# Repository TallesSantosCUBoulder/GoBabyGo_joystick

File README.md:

# GoBabyGo Joystick-Controlled Car
**ENGR140: First Year Engineering Projects - Colorado Mesa University**  
**Sponsor:** Talles Santos  
**Project Team:** Team Snow Munchers  
**Team Members:** Michael Riley (Civil Engineering)  
&emsp;&emsp;&emsp;&emsp;&emsp;&emsp;&emsp;&emsp; Francisco Cuen (Mechanical Engineering)  
&emsp;&emsp;&emsp;&emsp;&emsp;&emsp;&emsp;&emsp; Jaclyn Pellegrini (Mechanical Engineering)  
&emsp;&emsp;&emsp;&emsp;&emsp;&emsp;&emsp;&emsp;Caleb Kasayka (Mechanical Engineering)  
&emsp;  
&emsp;
&emsp;  
**Note: A large part of this README file references the [User Manual](/Reports/Users%20manual.pdf) and [Final Report](/Reports/Final%20Report%20First%20Draft%20-%20Snow%20Munchers.pdf) written by the members of the Snow Munchers Team. The printed circuit board (PCB) was designed, and the README was written and compiled, by Electrical and Computer Engineering Senior [Alyssa Jackson](https://github.com/aJax-EXE).**

## Introduction
“GoBabyGo” is a non-profit organization dedicated to providing children with limited mobility the opportunity to play independently by adapting motorized toy cars. Many children with mobility challenges struggle to press the pedal and steer simultaneously, making it difficult to operate the vehicle without constant assistance. Typical “GoBabyGo” modifications reroute the pedal wiring to a button mounted on the steering wheel, simplifying acceleration and improving usability.  

After multiple iterations, the final design operated successfully and remained within budget. It reliably controlled forward/backward motion and steering, and testing showed consistent performance with minimal drift. The system was safe, intuitive, and easy for children to use. Future work should focus on simplifying the steering circuit and adapting the design for broader use across different ride‑on car models to benefit more children.  

*A standin image of the completed modified car*  

## Project Overview
While the standard modifications help many children, some still find it difficult to press a button and steer at the same time. This project aims to create a more intuitive control system by replacing both the pedal and steering wheel with a single joystick. The joystick must control forward and backward motion as well as left and right steering, operate safely under 12 V and 3 A, and be implemented for under $200.  

### Design Requirements
Along with the functions that the car needs to reach from the the project overview, the following and specific requirements were needed:  
* Directional Control
    * Provide forward, reverse, left, and right motion; each direction successfully actuates correct motor behavior 10/10 trials with a response rate of .5 seconds. 
* Consistent Steering & Speed Response
    * Vehicle follows the same path in 5 repeated trials within acceptable tolerance (e.g., ±6 inches lateral drift over 10-15ft).
* 12V Maximum Power
    * Must not exceed 12V thought out the electrical system.
* Dashboard Fit
    * Total joystick assembly dimensions must not exceed 2.75 in (height) × 3.125 in (width). Zero interference points and no natural obstructions.
* Heat Limit
    * Must not exceed 113° over 15 minute time intervals.

###  Electrical Solutions
For this car, a modification was made for the movement. Using a joystick instead of a steering wheel and foot-powered pedals, the car can move forwards and backwards without restrictions, but turning left and right is altered. Instead of turning left and right without restriction, moving or holding the joystick in either direction causes the car to turn for only a set amount of time before stopping and waiting for another input. __This is to help keep the motors from stalling as ... ? (Include a video/gif of the car moving in all four directions with the joystick)__  

*The Full Circuit Diagram of the car*  
&emsp;  

The full construction of the circuit requires the following components:
* [3 IBT-2 BTS7960 High Current H-Bridge Motor Drivers](/Datasheets/BTS7960%20Motor%20Driver.pdf)  
&emsp;  
      
    *The Function diagram of an H-Bridge Controller*  
    &emsp;  

    * Full representation of the function of an H-Bridge Controller can be found in the above image. When an input is received, it sends a signal to the H-bridge motor controller which recognizes the voltage as a directional input and then outputs that signal into the motor itself. This allows for safe, effective, bi-directional movement. The H-bridge has a total of 12 attachment points. two for power in, two for power to motor, two for input detection (seen as “IN”), two for inhibiting direction (“INH”, two for ISs), a ground for the logic board (GND), and a 5.5V input for the logic board (“VCC”). This design will take advantage of all the inputs / outputs except for the SIs.
* [2 LM555 Timer Chips](/Datasheets/lm555.pdf)  
&emsp;  
      
    *Diagram of a 555 timer and the respective pins*  
    &emsp;  

    * A 555 timer is an integrated circuit that takes an electrical input and outputs a pulse over a certain interval of time. This component is needed to turn the front steering motor to a certain point so that the motor doesn’t overturn the mechanical component, breaking the car, and burning out the motor. Power is inputted through the VCC pin which powers the circuit (as seen in the above image). When a signal comes through the Trigger pin, it goes through the circuit within the 555 and then a capacitor and resistor attached to the discharge and threshold pins which controls how long a pulse is sent out of the output pin. For this project, the 555 is operated in monostable mode, meaning it sends out a singular pulse and then returns to its original state. To get the pulse to last for a certain time, the equation T=1.1RC where T is time, R is the strength of the resistor, and C is the value of the capacitor. For the motor a 1 second pulse is needed so values of a100kΩ resistor and a 10µF capacitor are needed.
* [A Joystick](/Datasheets/SANWA%20JLF-TP-8YT%20Joystick%20Instruction%20Manual.pdf)  
&emsp;  
      
    *Internal switching logic of the arcade joystick*  
    &emsp;  

    * The above image illustrates the internal switching logic of the joystick. The joystick has five wires with a gauge of 23 AWG (American Wire Gauge). These wires are connected to a circuit board via a connector. This system consists of four signal wires, each for a different switch that is also connected to the circuit board. The last wire serves as a 5V-12V source wire; the input (5V-12V) will flow through this wire and in return, will output through one of the four switches (possibly two) depending on which switch is compressed or activated. 
* [An RC Car](/Datasheets/BCP%20Sky908%20User%20Manual.pdf)
    * For this project an existing car was bought and provided to the group, but the car model used costs around $250 USD.

* [2 NPN Bipolar Junction Transistors](/Datasheets/2n2222a.pdf)  
&emsp;  
      
    *The circuit diagram of the pulse shaping module used in the car*  
&emsp;  
      
    *The 3D Model that represents what the working model looks like*  
&emsp;  

    * The transistors are the necessary part of the timing circuit. For the 555 to properly work, it needs sharp, high input. This is not as simple as it would seem because our joystick is mainly used in a “toggle” sense, where the driver will hold it left to turn left. After some testing, we realized that this toggled system would lead to the output of the 555 system always being held high. To fix this, we implemented what is called a pulse shaping module. This consists mainly of a capacitor momentarily allowing a transistor to drain a power source to ground, creating a quick pulse of electricity that the 555 timers can properly understand. The above images shows the pulse shaping module implemented into the design of the circuit and the 3D model of the completed PCB with all of its components.  
* [Joystick Mount](/3dModels/Joystick%20Mount%203.STL)
&emsp;  
      
    *The SolidWorks drawing of the joystick mount*  
    &emsp;  

    * The joystick already has two existing mounting holes, 0.278 inches in diameter, implemented into the factory design. With this, a CAD drawing was produced and integrated with these existing holes (see Appendix E). The design functions similar to a washer where it will mount on the original steering wheel location. Two bolts will run through the top (the side where the joystick extrudes), and below there will be two nuts securing the simple assembly in place. The above image consists of a SolidWorks drawing of the mount.  
* A 12V to 5V Voltage Step Down
    * Must be able to handle 3A of current and 15W of power.
* 6 100k Ohm Resistors
* 4 10k Ohm Resistors
* 4 10uF Capacitors
* A 12V Battery
    * The model of car used includes a 12V 7AH battery. Most electric kid cars run on 6V, but this system is designed for 12V. To use this system with a 6V battery, a voltage step down that goes from 6V to 5V, or rather a simple voltage divider, needs to be used to run the system properly.
* 2 Rolls of 20 AWG Wire
    * One red and one black preferred.  
* Female to Female Jumper wires  

The circuit starts at the battery going into the two gearboxed motors of the car and the voltage step down. The 5V from the stepdown powers the rest of the system: all three of the motor drivers and the two 555 timer circuits. While the forward and backwards motor drivers are only activated with the direct signal from the joystick, the left and right one first goes through there respective timing circuit to give the proper timed signal.  

*The Full PCB model for the car*  
&emsp;  

The PCB holds the resistors, capacitors, and transistors that make up the timing circuit, as well as all of the connectors necessary for both powering the board, connecting the joystick to the motor drivers, and for the motor drivers themselves.

## Hardware Setup and How to Operate
For the complete instructions on how to modify the car to replicate the project, perform maintainence, and for a full list of tools needed and how to use, refer to the [User Manual](/Reports/User%20Manual%20Outline.pdf) written by the Snow Munchers.

### Recommendations for Operation
Before general use, it is recommended that:  
* The driver does not exceed 77lbs
* The car avoids liquid 
* The car is not driven in the rain	 
* The car avoids sharp drops offs like curbs

## Results
### Overview
The electric ride on car was evaluated against the specified design requirements through structed user testing and system performance checks. Each criterion, directional control, steering consistency, power limit, heat limit, and size requirement, was assessed during real world operation to ensure the design met both functional and safety expectations. Users operated the vehicle under normal conditions, allowing the team to observe control, responsiveness, and overall usability. The system was required to satisfy all evaluation criteria in order to be considered successful. Testing results showed that the ride on car met all the design requirements, demonstrating reliable performance, safe operations, and suitability for its intended use.  
&emsp;  
### CRITERIA 1 – DIRECTIONAL CONTROL
Provide forward, reverse, left, and right motion; each direction successfully actuates correct motor behavior 10/10 trials with a response rate of .5 seconds.  

* **PURPOSE OF EVALUATION**: The purpose of the directional control test is to ensure that the electric ride on car responds accurately and reliably to user inputs. Effective directional control is essential for safe operations, as it allows the user to intentionally move the vehicle forward, backward, and laterally, ensuring the car can be maneuvered smoothly during normal operation and while navigating obstacles or turns. 

* **TESTING METHODS**: The evaluation of this design criteria requires that the user manually push the joystick in each direction, forward, backward, left, and right. This was tested in two ways, a static test, elevating the car off a flat surface so that the wheels can spin freely allowing the testers to visually see the steering response. And a dynamic test, driving the car through a specially crafted course designed with turns and corners to test the steering compacity while in motion. For the setup, the car was supported above a flat surface using four wooden 2 by 4 blocks, ensuring that all the wheels were fully suspended and unrestricted in rotation. This configuration eliminated ground friction and external load effects. Allowing isolated evaluation of the motor and steering response. With the vehicle secured, the joystick was actuated individually in the forward, reverse, left, and right directions. Observations were made to confirm correct wheel rotation direction, steering actuation, and immediate system response corresponding to each input. Any unintended motion, delay, or incorrect direction would indicate a fault in the signal interpretation or motor control. For the dynamic control test the electric ride on car was operated on a flat indoor surface and driven through a predefined course designed to replicate realistic operating conditions. The course consisted of straight sections, gradual turns, and sharp corners. Requiring continuous directional input adjustments. The user controlled the vehicle solely via the joystick, executing directional changes while the car remained in motion. This test evaluated the system’s ability to interpret joystick input under load, maintain control during directional transitions, and execute smooth turning without loss of stability or responsiveness. 

* **RESULTS & DISCUSSION**: The electric ride on car demonstrated correct directional response during both static and dynamic testing. In the static response test, joystick inputs in all four directions resulted in correct wheel movement with no observed latency, incorrect rotation, or unintended behavior. During the dynamic testing, the vehicle successfully followed the predetermined course and executed directional changes while in motion. The system maintained full responsiveness and directional accuracy thought out all test runs. No failures or loss of control were observed. As a result, the directional control system achieved a 100% success rate across all tests. The results indicated that the directional control system functions as intended under both unloaded and operational conditions. The static test confirmed control signal interpretation and motor actuation, while the dynamic test verified reliable performance under load. Although quantitative data was not collected, consistent qualitative performance across multiple trials demonstrates that the system meets the directional control requirements. The ability to maintain accurate direction changes while motion indicates sufficient control logic, motor response, and system integration. Therefore, the direction control design requirement was fully satisfied.  

### CRITERIA 2 – STEERING CONSISTENCY
Vehicle follows the same path in 5 repeated trials within acceptable tolerance (e.g., ±6 inches lateral drift over 10-15ft).  

* **PURPOSE OF EVALUATION**: The purpose of the steering consistency requirement is to ensure that the vehicle responds predictably and repeatably and repeatably to identical steering inputs. Consistent steering behavior is essential for user confidence, safe operation, and accurate maneuvering. This requirement verifies that the steering system produces uniform turning behavior without variation or drift during repeated use. 

* **TESTING METHODS**: Steering consistency was assessed using a straight-line deviation test. The vehicle was commanded to drive forward with a fixed joystick input while lateral deviation from a defined centerline was measured. The test evaluates the vehicle’s ability to maintain a straight trajectory under constant input. This method demonstrates whether the steering system produces predictable and repeatable behavior, which directly impacts controllability and user confidence in the finished product. For the setup, the steering consistency test was conducted on a flat, level surface to minimize external influences. A straight reference line was established using a tape measure at a fixed distance placed longitudinally along the test path. The electric ride on was aligned so that its centerline coincided with the reference line at the starting position. The vehicle was positioned at a consistent starting distance for each trial to ensure repeatability. During testing, the car was allowed to travel forward along the reference line while lateral deviation from the centerline was visually monitored and measured relative to the ruler. All tests were performed under identical surface and environment conditions to ensure consistent results. 

* **RESULTS & DISCUSSION**: The straight-line steering consistency test produced lateral drift across multiple trials and test length ranging from approximately 10 – 15ft. measured drift values varied significantly between trials, indicating nonuniform steering behavior under constant joystick input. Server trials remained within the ±6 in acceptance tolerance, deviations were small and showed no progressive drift over the test distance. However few outliers appeared in the tests but they were ruled out for being user error and were taken note of but not deemed important to the over all trials. Within this acceptance range, deviations were small and showed no progressive drift over the test distance. The compliant data demonstrates repeatable straight line tracking performance under consistent input conditions. The in tolerance results indicate that the steering system is capable of maintaining an acceptably straight trajectory when commanded with fixed forward input. The limited magnitude of lateral deviation suggests that the mechanical steering alignment and control response are sufficient for stable, predictable operation in the finished design. These results support the conclusion that, within defined performance limits, the steering system meets the consistency requirement. Maintaining deviation with ±6 inches ensures adequate controllability and user confidence during straight line motion.  

### CRITERIA 3 – POWER LIMIT
Must not exceed 12V thought out the electrical system.  

* **PURPOSE OF EVALUATION**: The purpose of the power limit requirement is to ensure that the electric ride on car operates within safe electric and mechanical limits. Restricted power output prevents excessive speed, reduces stress on system components such as the motor, battery, and drivetrain, and minimizes potential safety risks to the user. This requirement ensures controlled performance while maintaining reliability and compliance with design constraints for the finished project. 

* **TESTING METHODS**: To test, the power limit requirement was evaluated by measuring electrical current and voltage at key point throughout the vehicles electrical system. A multimeter was used to monitor voltage and current in selected wiring segments supplying the motor and control electronics during operation. Testing verified that system voltage remained below 12 V and that operating current did not exceed the specified limit of a 3 amp under normal driving conditions. Measurements were taken while the vehicle was powered and active to ensure compliance under realistic load conditions. For the setup, power limit testing was conducted using a digital multimeter to measure voltage and current at multiple points within the vehicle’s electrical system. Measurement locations included the batter output, motor supply lines, and control circuit wiring to capture representative operating conditions. The car was powered on and operated under normal operating conditions while the multimeter probes were connected in series for current measurement and in parallel for voltage measurement. Tests were performed while the vehicle was stationary and during motion to account for load variation. All measurements were taken with the system fully assembled to reflect real operating conditions. 

* **RESULTS & DISCUSSION**: Power limit testing confirmed that the electrical system operated within the defined constraints during all the testing conditions. Measured system voltage remained below the maximum allowable limit of 12V, and operating current did not exceed 3 amps at any monitored location. All measurements points across the battery, motor supply, and control wiring remained within the specified limits under both stationary and dynamic operating conditions, as a results, the power limit requirements was successfully met for all tests. The results confirm that the electrical power system operates within the specified voltage and current limits under normal operating conditions. Maintaining voltage below 12 V and current at or below 3 amps ensures safe operation of the motor and control electronics while reducing the risk of overheating, electrical stress, and components failure. Compliance with the power limit requirement indicates that the selected electrical components and system configuration are appropriately matched to the vehicle’s performance needs. This controlled power outage contributes to overall system reliability and user safety, supporting the suitability of the design for its intended application.  

### CRITERIA 4 – HEAT LIMIT
Must not exceed 113° over 15 minute time intervals.  

* **PURPOSE OF EVALUATION**: The purpose of the heat limit requirement is to ensure that the electrical and mechanical components of the electric ride on car operate within safe temperature ranges during normal use. Limiting heat buildup prevents thermal damage, reduced the risk of components failure, ensures user safety. This requirements supports system reliability longevity and consistent performance throughout operation. 

* **TESTING METHODS**: The heat limit requirement was evaluated by monitoring temperature during sustained operation. An Arduino based temperature sensing system was connected to the motor to continuously monitor thermal performance. The motor was operated continuously for a duration of 15 minutes under normal operating conditions. Temperature readings were observed to determine whether the motor temperature remained below the maximum allowable limit of 113 °F throughout the test period. For the setup, the heat limit was conducted using an Arduino microcontroller interfaced with a temperature sensor mounted directly to the motor casing to measure operating temperature. The sensor was secured to ensure consistent thermal contact and accurate temperature readings throughout the test. The electric ride on car was placed in a stationary configuration to allow continuous motor operation without external interruptions. Power was supplied under normal operating voltage, and the motors were run continuously for a 15 minute duration. Temperature reading were monitored in real time through the Arduino system to verify that the motor temperature remained below the maximum allowable limit of 113 °F for the entire test period.

* **RESULTS & DISCUSSION**: The heat limit requirement was considered satisfied based on qualitative observation during vehicle operation. Although a full 15 minute controlled temperature test was not completed due to time constraints, the motor was operated during multiple system tests without exhibiting signs of excessive heat build up. Though these test, the motor maintained stable performance with no observable thermal degradation, shut down, or adverse response related to heat generation. Based on the motors behavior during externed use and the absence of overheating indicators, the system was determined to operate within acceptable thermal limits. Although a full duration heat test was not completed, the observed system behavior during extended operations indicted that the motor operates within acceptable thermal limits. The absence of thermal issues during sustained use suggests that the selected motor and power configuration are sufficient for the intended operating conditions. While additional quantitative temperature data would strengthen validation, the qualitative results support the conclusion that the heat generation does not pose a safety or reliability concern for the current design. Future testing with continuous temperature logging over longer duration recommended to further validate thermal performance and confirm compliance under all operating scenarios.  

### CRITERIA 5 – SIZE REQUIREMENT
Total joystick assembly dimensions must not exceed 2.75 in (height) × 3.125 in (width). Zero interference points and no natural obstructions.  

* **PURPOSE OF EVALUATION**: The joystick components were required to fit within a designated envelope of 2.75in x 3.125 in space to ensure proper integration with the vehicle. Maintaining this size constraints prevents interference with vehicle operation, preserved drivability, and reduced the likelihood of accidental contact or mechanical damage during regular use. A compact fit also supports ergonomic accessibility for the user while allowing the control system to be securely mounted and protected within the vehicle structure.  

* **TESTING METHODS**: Size evaluation was conducted through a physical fitment verification and user interaction testing. The control circuit board was designed and assembled to conform to the allocated  dashboard of  2.75 in x 3.125 in. prior to permeant installation, the joystick components were temporally secured in the location using tape to allow visual and dimensional comparison with he available space. Once loosely secured, the vehicle was operated in a simulated use scenario. Testers interacted with the ride on car as a child user would, ensuring that the joystick and associated components did not obstruct operation, restrict movement, or practical useability of the installed parts.

* **RESULTS & DISCUSSION**: During size evaluation, the joystick mount component required four design iterations due to improper fit within the allocated dashboard space. Each reprint addressed dimensional and alignment issues until the final mount achieved a secure and accurate fit. The circuit board and associated wiring were successfully integrated within the design rea and remained neatly secured throughout testing. No components were exposed or positioned in a way that could be easily accessed or damaged during normal use. Once fully installed, all components fit securely within the available space without requiring further adjustment. These results confirm that the size requirement was met in the final configuration. Safe security of critical control components ensures the physical compatibly with the vehicle and is suitable for real-world use. Proper fitment directly affects drivability, user interaction, and long-term durability. Particularly in a ride on device intended for child use. Components that excess the allocated space or are improperly positioned introduce risks of accidental contact, interference during operation, or mechanical damage over time. The testing approach verifies dimensional compliance, simulating realistic user interaction. Supporting safe operation and reinforcing the overall robustness of the design.  

### Conclusion 
The electric ride on car joystick integration designed by the Snow Munchers team wad successfully evaluated against the defined design requirement using a combination of user testing, qualitative observation, and targeted system checks. The vehicle demonstrated reliable directional control and acceptable steering consistency under controlled testing conditions. Supporting predictable and safe maneuverability. Electric testing confirmed operation within the specified power limits, ensuring system safety and component reliability. Thermal performance did not present observable issues during extended operation, indicating the heat generation remains within acceptable bounds for the intended use. Additionally, the control components were successfully integrated within the allocated size constraints, preventing interference with drivability and reducing the risk of damage during regular use. Indicating the final design meets the primary functional, safety, and usability criteria created for the projects solid foundation and future refinement.  
&emsp;  

## Next Steps
Firstly, the telecontrol should be reattached. This feature was initially implemented into the car for safety, but the snow munchers did not have time to fully integrate this. To re-implement this feature, a second PCB would have to be printed to allow for toggleable control between the IBT-2 motor drivers and the standard relay. This could be done most simplistically with 4 transistors for each motor. Two to allow for flow from the telecontrol relay and the other two to allow for flow from the joystick. The second reintegration should be rewiring the lights. The old lights are already attached and ready to run, however they need to be wired to a new power to turn on with the car. Similarly, the sound system can be easily repaired; however, the old speaker was damaged when removed, so a replacement would need to be purchased and reinstalled inside the dashboard.

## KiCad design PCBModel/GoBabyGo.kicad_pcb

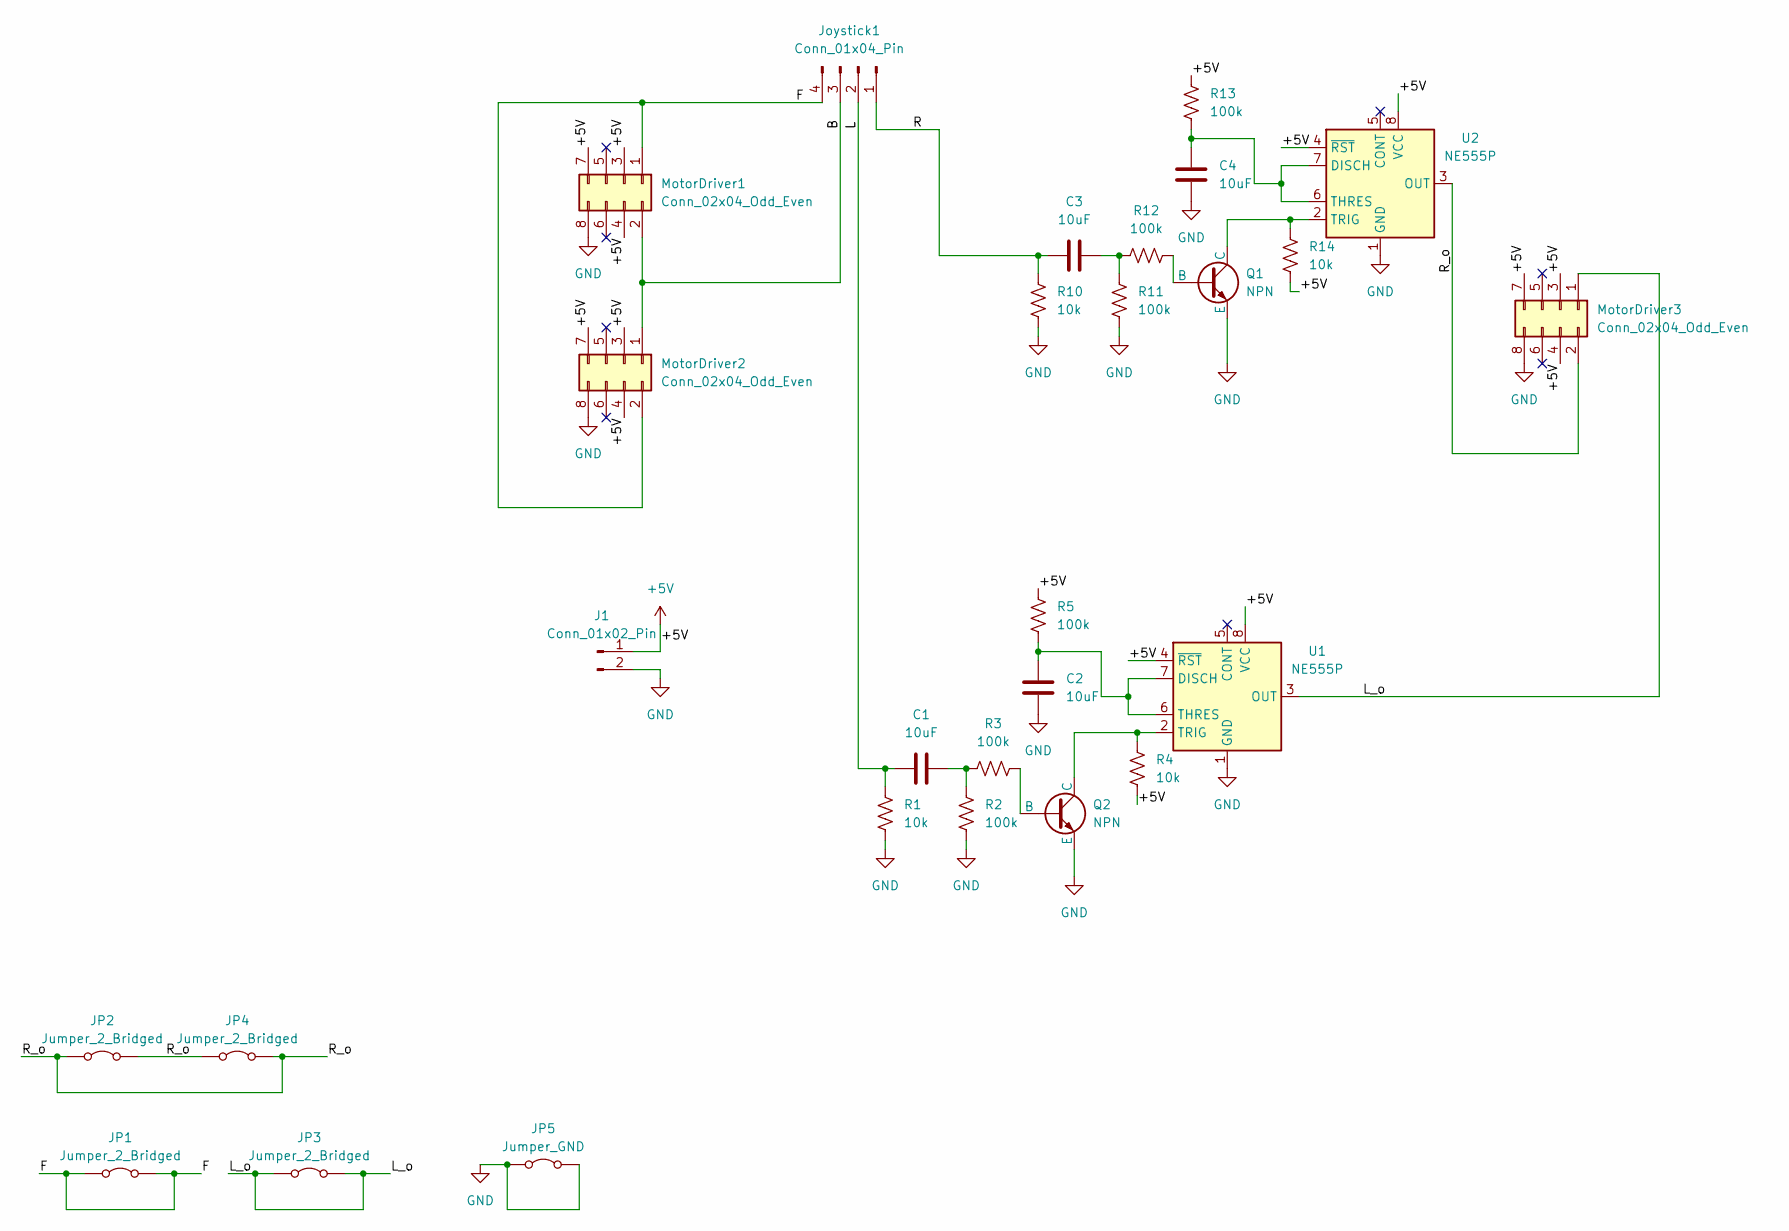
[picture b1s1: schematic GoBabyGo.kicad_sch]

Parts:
C1, C2, C3, C4: 10uF; C_Axial_L3.8mm_D2.6mm_P7.50mm_Horizontal
J1: Conn_01x02_Pin; PinHeader_1x02_P2.54mm_Horizontal
JP1, JP2, JP3, JP4: Jumper_2_Bridged; R_Axial_DIN0207_L6.3mm_D2.5mm_P5.08mm_Vertical
JP5: Jumper_GND; R_Axial_DIN0207_L6.3mm_D2.5mm_P5.08mm_Vertical
Joystick1: Conn_01x04_Pin; PinHeader_1x04_P2.54mm_Horizontal
MotorDriver1, MotorDriver2, MotorDriver3: Conn_02x04_Odd_Even; PinHeader_2x04_P2.54mm_Vertical
Q1, Q2: NPN; TO-92_Wide
R1, R4, R10, R14: 10k; R_Axial_DIN0207_L6.3mm_D2.5mm_P7.62mm_Horizontal
R2, R3, R5, R11, R12, R13: 100k; R_Axial_DIN0207_L6.3mm_D2.5mm_P7.62mm_Horizontal
U1, U2: NE555P; DIP-8_W7.62mm

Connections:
+5V: J1.1, MotorDriver1.3, MotorDriver1.4, MotorDriver1.7, MotorDriver2.3, MotorDriver2.4, MotorDriver2.7, MotorDriver3.3, MotorDriver3.4, MotorDriver3.7, R4.2, R5.1, R13.1, R14.2, U1.4 (~RST), U1.8 (VCC), U2.4 (~RST), U2.8 (VCC)
/B: Joystick1.3, MotorDriver1.2, MotorDriver2.1
/F: JP1.1 (A), JP1.2 (B), Joystick1.4, MotorDriver1.1, MotorDriver2.2
/L: C1.1, Joystick1.2, R1.1
/L_o: JP3.1 (A), JP3.2 (B), MotorDriver3.1, U1.3 (OUT)
/R: C3.1, Joystick1.1, R10.1
/R_o: JP2.1 (A), JP2.2 (B), JP4.1 (A), JP4.2 (B), MotorDriver3.2, U2.3 (OUT)
GND: C2.2, C4.2, J1.2, JP5.1 (A), JP5.2 (B), MotorDriver1.8, MotorDriver2.8, MotorDriver3.8, Q1.3 (E), Q2.3 (E), R1.2, R2.2, R10.2, R11.2, U1.1 (GND), U2.1 (GND)
unnamed: C1.2, R2.1, R3.1
unnamed: C3.2, R11.1, R12.1
unnamed: Q1.2 (B), R12.2
unnamed: Q1.1 (C), R14.1, U2.2 (TRIG)
unnamed: Q2.2 (B), R3.2
unnamed: Q2.1 (C), R4.1, U1.2 (TRIG)
unnamed: C2.1, R5.2, U1.6 (THRES), U1.7 (DISCH)
unnamed: C4.1, R13.2, U2.6 (THRES), U2.7 (DISCH)

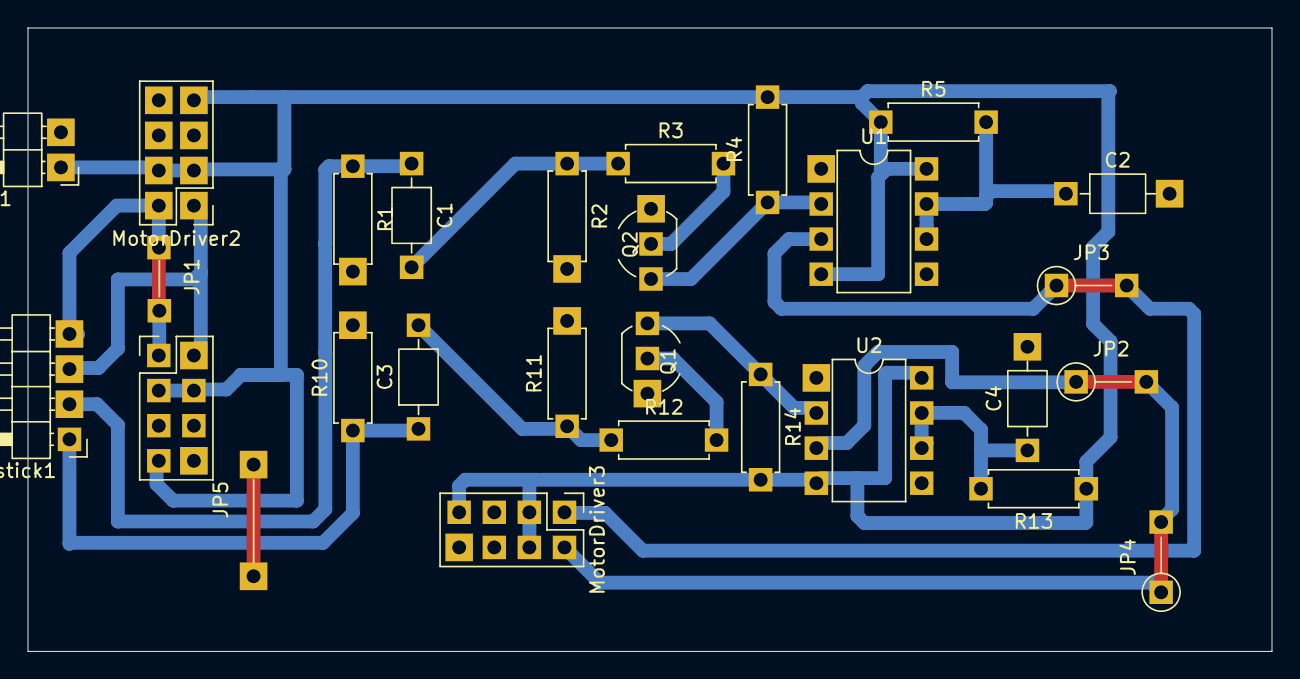
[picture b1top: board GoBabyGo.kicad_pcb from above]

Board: 2 copper layers, 90.0 x 45.1 mm, 28 parts (0 on the bottom side), 16 nets.

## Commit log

2026-04-20 Added Images, datasheets, and PCB Model to the Github
2026-04-20 Renamed Images
2026-04-21 Minor PCB Model Fix
2026-04-21 PCB review.
2026-04-28 Small addition
2026-04-28 Intoduction to README
2026-04-28 Beginning of Github README Formatting
2026-04-28 Format update
2026-04-28 Start of electrical solutions select
2026-04-28 README Update and added image
2026-04-28 Add section about the 555 timer and minor changes to the image
2026-04-28 Added to the README and some image changes
2026-04-28 Update to the correct image
2026-04-28 Update the image in README
2026-04-28 the correct image this time
2026-04-28 Trying out the linking feature for the README
2026-04-28 Added component list
2026-04-28 Added broken links and image to go with it
2026-04-28 schematic update
2026-04-29 Updated links
2026-05-01 Start of the README Report
2026-05-01 Format test
2026-05-04 Adding some descriptions
2026-05-05 Update to the README
2026-05-05 Added link for Mount and some more updates for the README
2026-05-05 Mahor changes to the README
2026-05-06 Added Images and updated README with them
2026-05-06 update the README
2026-05-06 Another formatting fix to the README
2026-05-06 Spacing Update
2026-05-06 README Update
2026-05-06 Fixed Spacing
2026-05-08 Almost done README, Updated reports, and added images
2026-05-08 Final touches on the README
2026-05-08 Final README; to be reviewed by team
2026-05-08 Final README for real for real
2026-05-08 Attempted formatting fix for the README
2026-05-08 Another attempt
2026-05-08 New fix to the format
2026-05-08 Slmall typing update for the README
2026-05-12 Added the slide show for presentation, a gif, and a pdf of the README
